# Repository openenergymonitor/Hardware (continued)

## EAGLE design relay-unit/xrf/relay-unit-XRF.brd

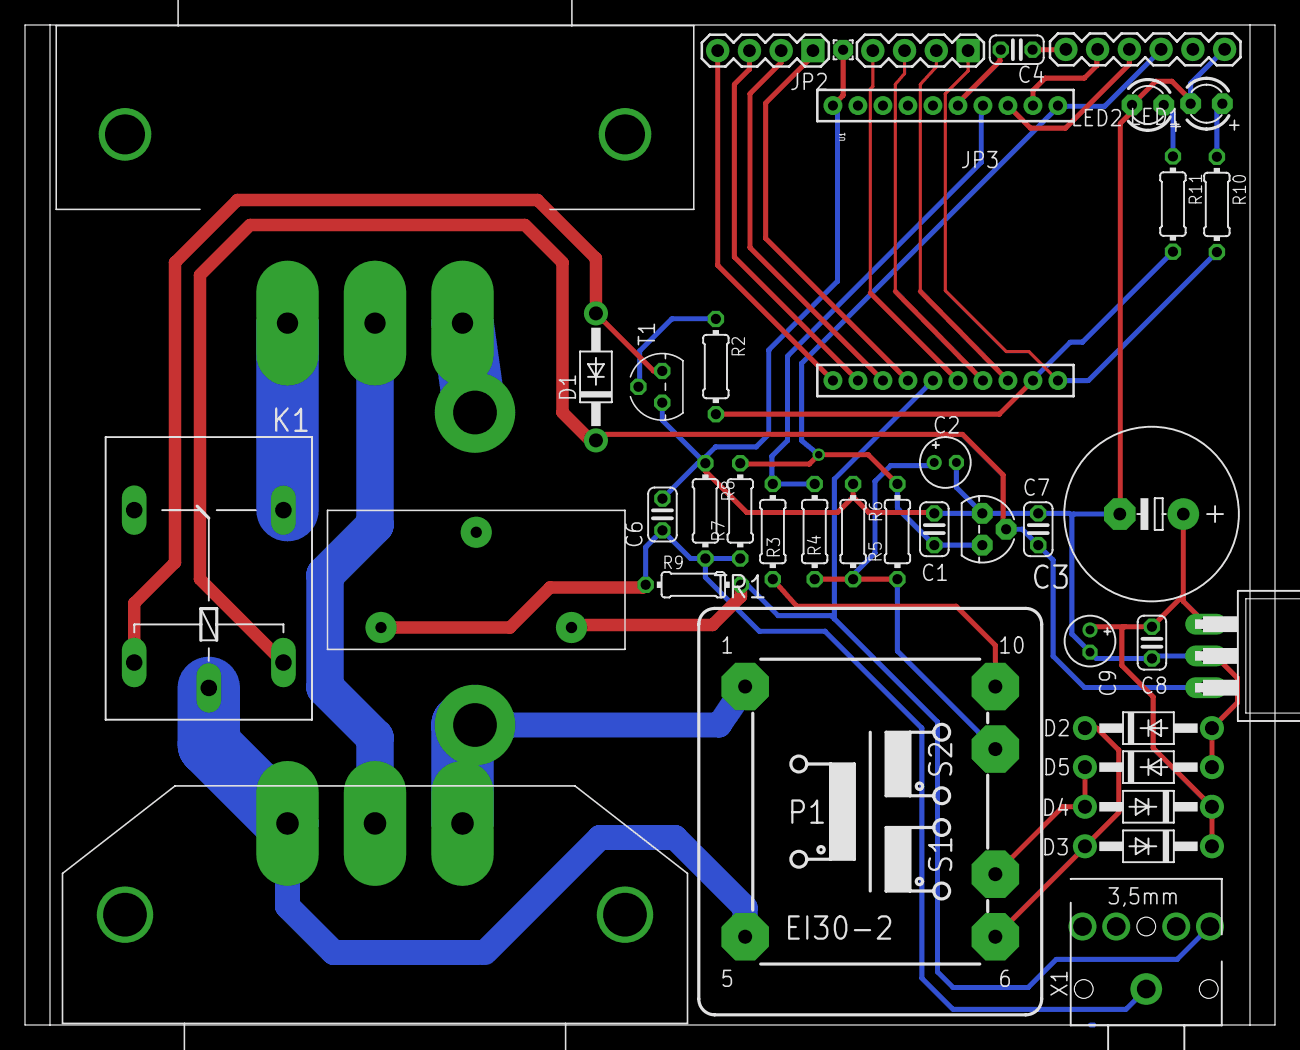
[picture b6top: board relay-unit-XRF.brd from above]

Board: 2 copper layers, 100.0 x 80.0 mm, 39 parts (0 on the bottom side), 32 nets.

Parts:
C1, C4, C7, C8: 0.1u; C025-024X044
C2, C9: 10uf; E1,8-4
C3: 2200uF; E5-13
C6: 10uF; C025-024X044
D1, D2, D3, D4, D5: 1N4004; DO41-10
IC1: TO92
IC2: 7805T; TO220H
JP1: FTDI_BASICPTH; FTDI_BASIC
JP2, JP3: 1X04
K1: G5LE
LED1, LED2: LED3MM
PAD4: 1,6/0,8
R2: 10k; 0204/7
R3, R4: 0204/7
R5, R6, R7, R8: 470k; 0204/7
R9, R10, R11: 100R; 0204/7
T1: 2N3904; TO92
TR1: EI30-2
U1: RFµ-328-SOCKET
U$1: TESTTEST; TEST
U$2: AC_IN
U$3: CT
X1: STEREOJACK; STX3100

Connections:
5V: C7.1, D1.C, IC1.2, IC2.3, K1.1
GND: C1.2, C2.-, C3.-, C6.2, C7.2, C8.2, C9.-, D2.A, D5.A, IC1.1, IC2.2, JP1.GND, LED1.K, LED2.K, PAD4.1, R6.1, R8.1, T1.3, U1.10
unnamed: JP1.RXI, U1.2
unnamed: JP1.TXO, U1.3
unnamed: C4.2, JP1.DTR
unnamed: JP2.1, U1.14
unnamed: JP2.2, U1.13
unnamed: JP2.3, U1.12
unnamed: JP2.4, U1.11
unnamed: C4.1, U1.5
unnamed: JP3.1, R10.2, U1.20
unnamed: JP3.2, U1.18
unnamed: JP3.3, U1.17
unnamed: JP3.4, U1.16
unnamed: C3.+, C8.1, C9.+, D3.C, D4.C, IC2.1
unnamed: R3.2, TR1.10
unnamed: R2.1, T1.2
unnamed: D1.A, K1.2, T1.1
unnamed: R2.2, R11.2, U1.19
unnamed: K1.S, U$1.LIVE
unnamed: TR1.1, U$1.NEUTRAL, U$2.NEUTRAL
unnamed: C2.+, R4.1, R5.1, R6.2, TR1.9
unnamed: D2.C, D3.A, TR1.6
unnamed: R9.2, U1.15, U$3.CT2, X1.5
unnamed: C6.1, R7.1, R8.2, R9.1, U$3.CT1, X1.1
unnamed: R3.1, R4.2, U1.4
unnamed: D4.A, D5.C, TR1.7
unnamed: U$1.EARTH, U$2.EARTH
unnamed: LED1.A, R10.1
unnamed: LED2.A, R11.1
unnamed: K1.P, TR1.5, U$2.LIVE
VCC: C1.1, IC1.3, JP1.VCC, R5.2, R7.2, U1.1
